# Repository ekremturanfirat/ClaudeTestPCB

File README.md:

# PCBDesignWClaude — 3-Phase BLDC ESC (ESP32-WROOM-32E)

KiCad project for a 3-phase brushless motor ESC.

- **MCU:** ESP32-WROOM-32E, soldered SMD directly onto the PCB (no plug-in module)
- **Input:** 12–36V DC
- **Target continuous phase current:** ~5–10A
- **Control/telemetry:** UART + CAN bus
- Design follows [METU PowerLab PCB design rules](https://github.com/odtu/Powerlab/blob/master/KiCAD/PCB_DESIGN_RULES.md)
  and uses parts exclusively from [PowerLabKiCadLibraries](https://github.com/odtu/PowerLabKiCadLibraries).

## Status
- [x] GitHub repo created
- [x] ESP32-WROOM-32E added to PowerLabKiCadLibraries (odtu/PowerLabKiCadLibraries#2, merged)
- [x] Library additions + fixes (power symbols, mounting holes, fiducials, test pads, net ties, ESP32 footprint fix): odtu/PowerLabKiCadLibraries#3 (merged)
- [x] Schematic Rev B: full rebuild per the PowerLab rules; kicad-cli ERC 0 errors, netlist verified (see [hardware/ARCHITECTURE.md](hardware/ARCHITECTURE.md))
- [x] Library fixes found during layout (exposed pads, mask margins, logo/QR graphics, ESP32 3D model): odtu/PowerLabKiCadLibraries#5 (merged)
- [x] PCB Rev B: 4 layers, 100 × 90 mm; kicad-cli DRC 0 errors / 0 unconnected / 0 parity (see [hardware/ARCHITECTURE.md](hardware/ARCHITECTURE.md#pcb-rev-b))
- [x] Fab outputs: Gerber + drill zip, BOM, position file, assembly drawings in [hardware/fab](hardware/fab/README.md)

## Layout
- `hardware/` — KiCad project

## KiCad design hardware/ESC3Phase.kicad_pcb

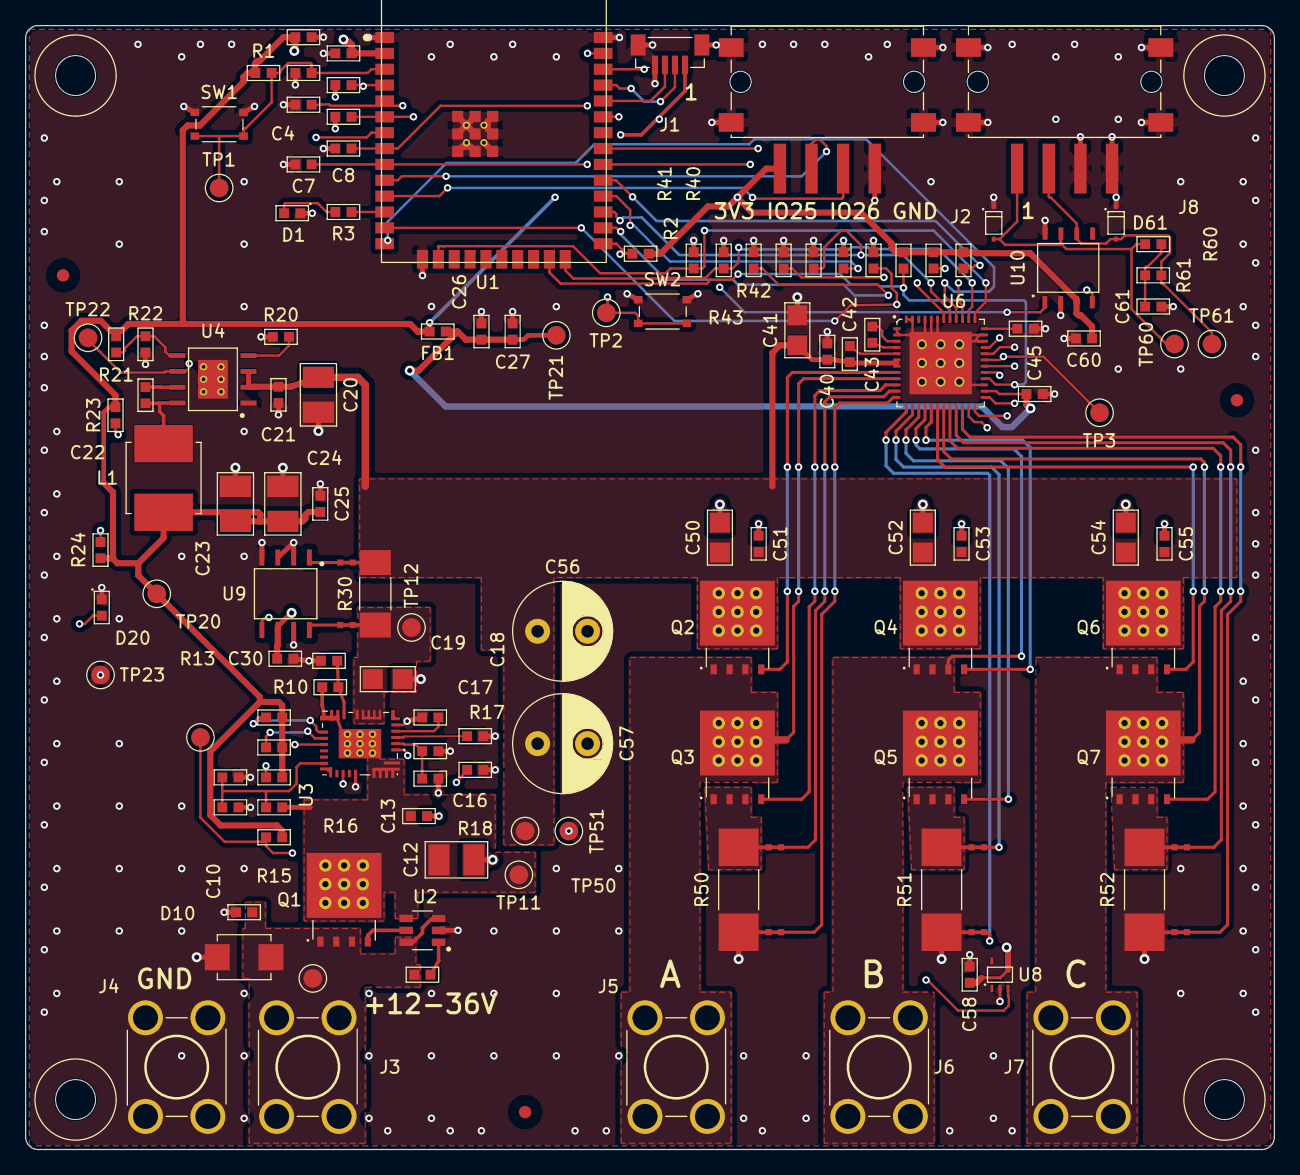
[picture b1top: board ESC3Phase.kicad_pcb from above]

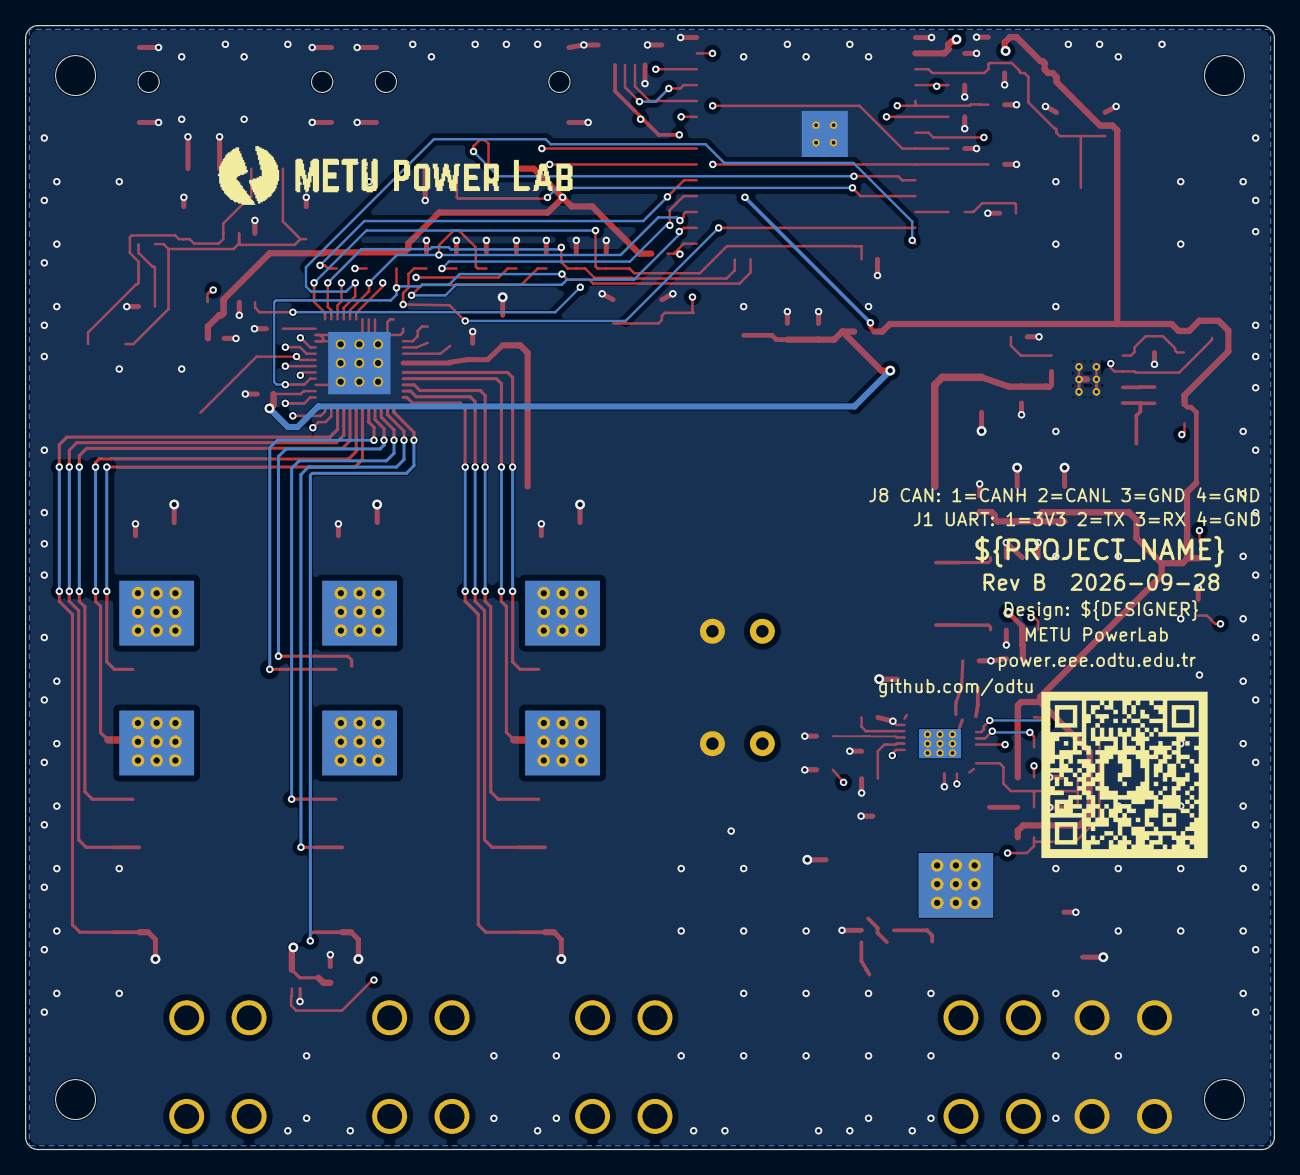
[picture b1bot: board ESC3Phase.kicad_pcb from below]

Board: 4 copper layers, 100.0 x 90.0 mm, 141 parts (2 on the bottom side), 79 nets.

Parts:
C1: 22 µF; 0603_Medium
C2, C14, C18, C22, C25, C27, C30, C45, C58, C60: 100 nF; 0603_Medium
C3, C44: 1 µF; 0603_Medium
C4, C5, C6, C7, C8, C15: 220 pF; 0603_Medium
C10, C13, C21, C40, C51, C53, C55: 100 nF 100V; 0603_Medium
C11: 100 nF 16V; 0603_Medium
C12, C20: 4.7 µF 100V; 1210_Medium
C16: 22 pF; 0603_Medium
C17: 1 nF; 0603_Medium
C19, C41, C50, C52, C54: 10 µF 100V; 1206_Medium
C23, C24: 47 µF; 1210_Medium
C26: 10 µF; 0603_Medium
C42: 1 µF 100V; 0603_Medium
C43: 47 nF 100V; 0603_Medium
C56, C57: 100 µF 63V; 8.00x13.50mm
C61: 4.7 nF; 0603_Medium
D1, D20: Green; 0603_Medium
D10: SMBJ36CA-13-F; DO-214AA
D60, D61: CDSOD323-T24SC; SOD-323
FB1: BLM18EG221SN1D; 0603_Medium
FID1, FID2, FID3: Fiducial_1mm_Mask2mm
H1, H2, H3, H4: M3_NPTH
J1: UART; 2147210040
J2: EXPANSION; 384471-E
J3: VIN+; 7770
J4: GND; 7770
J5, J6, J7: PHASE; 7770
J8: CAN; 384471-E
L1: 4.7µH; 6x5_7mm
LOGO1: METUPowerLab_Logo_30mm
NT1, NT2, NT3, NT4, NT5, NT6, NT7, NT8: NetTie_2_0.5mm
Q1, Q2, Q3, Q4, Q5, Q6, Q7: NTMFS006N08MC; 8-PowerTDFN(5x6mm)
QR1: METUPowerLab_QRCode_13.3mm
R1, R2, R13, R14, R15, R16, R40, R41, R42, R43, R44, R45, R46, R47, R48, R49: 10 kOhm; 0603_Medium
R3, R24: 1 kOhm; 0603_Medium
R10: 120 Ohm; 0603_Medium
R11: 866 kOhm; 0603_Medium
R12: 118 kOhm; 0603_Medium
R17: 3.65 kOhm; 0603_Medium
R18: 1.33 kOhm; 0603_Medium
R20: 54.9 kOhm; 0603_Medium
R21: 110 kOhm; 0603_Medium
R22: 47 kOhm; 0603_Medium
R23: 100 kOhm; 0603_Medium
R30: 5 mOhm; 2010
R50, R51, R52: 2 mOhm; 2512
R60, R61: 56 Ohm; 0603_Medium
SW1: RESET; TL6330AF200Q
SW2: BOOT; TL6330AF200Q
TP1: EN; Pad_D1.5mm
TP2: BOOT; Pad_D1.5mm
TP3: SPI_SCLK; Pad_D1.5mm
TP10: VIN_RAW; Pad_D1.5mm
TP11: +VBUS; Pad_D1.5mm
TP12: +VBUS_EFUSE; Pad_D1.5mm
TP13: EFUSE_PGOOD; Pad_D1.5mm
TP20: +3V3_MCU; Pad_D1.5mm
TP21: +3V3_A; Pad_D1.5mm
TP22: BUCK_PG; Pad_D1.5mm
TP23, TP51: GND; Pad_D1.5mm
TP50: +VBUS_PROT; Pad_D1.5mm
TP60: CANH; Pad_D1.5mm
TP61: CANL; Pad_D1.5mm
U1: ESP32-WROOM-32E
U2: LM74700QDBVRQ1; SOT-23-6_DBV
U3: PTPS16890VMAR; 23-LQFN-CLIP_(VMA)
U4: LMR38020FSDDAR; 8-SOICPower
U6: DRV8323RSRGZT; 48-VQFN
U8: TMP235A4DCKR; SC-70-5
U9: INA240A1DR; 8-SOIC
U10: SN65HVD230DR; 8-SOIC

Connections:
+3V3_A: C26.1, C27.1, C30.1, C45.1, C58.1, FB1.2, TP21.1, U6.26, U8.4, U9.6
+3V3_MCU: C1.1, C2.1, C23.1, C24.1, C25.1, C60.1, FB1.1, J1.1, J2.1, L1.2, R1.1, R2.1, R13.2, R14.2, R15.2, R16.2, R21.1, R23.2, R24.1, R47.2, R48.2, R49.2, TP20.1, U1.2, U10.3
+VBUS: C12.1, C13.1, Q1.3, R10.1, R11.1, TP11.1, U2.4, U3.10, U3.22, U3.23, U3.24
+VBUS_EFUSE: C19.1, NT1.1, R30.1, TP12.1, U3.7, U3.8
+VBUS_PROT: C20.1, C21.1, C40.1, C41.1, C42.1, C50.1, C51.1, C52.1, C53.1, C54.1, C55.1, C56.1, C57.1, NT2.1, Q2.3, Q4.3, Q6.3, R30.2, TP50.1, U4.2, U4.3, U6.6, U6.7
/Communication/CANH: D60.1, J8.1, R60.1, TP60.1, U10.7
/Communication/CANL: D61.1, J8.2, R61.2, TP61.1, U10.6
/Communication/CAN_SPLIT: C61.1, R60.2, R61.1
/DC-Bus Current Sensing/IBUS_SNS_N: NT2.2, U9.1
/DC-Bus Current Sensing/IBUS_SNS_P: NT1.2, U9.8
/Gate Drive/CPH: C43.1, U6.4
/Gate Drive/CPL: C43.2, U6.3
/Gate Drive/DVDD: C44.1, U6.36
/Gate Drive/VCP: C42.2, U6.5
/MCU Core/BOOT: R2.2, SW2.1, TP2.1, U1.25
/MCU Core/EN: C3.1, R1.2, SW1.1, TP1.1, U1.3
/MCU Core/EXP1: J2.2, U1.10
/MCU Core/EXP2: J2.3, U1.11
/MCU Core/LED_STATUS: R3.1, U1.12
/MCU Core/UART_RXD: J1.3, U1.34
/MCU Core/UART_TXD: J1.2, U1.35
/Power Input & Protection/EFUSE_DVDT: C18.1, U3.4
/Power Input & Protection/EFUSE_EN: C15.1, R11.2, R12.1, U3.16
/Power Input & Protection/EFUSE_ILIM: R18.1, U3.1
/Power Input & Protection/EFUSE_IMON: C16.1, R17.1, U3.2
/Power Input & Protection/EFUSE_IREF: C17.1, U3.3
/Power Input & Protection/EFUSE_PGOOD: R15.1, TP13.1, U3.19
/Power Input & Protection/EFUSE_SCL: R14.1, U3.12
/Power Input & Protection/EFUSE_SDA: R13.1, U3.11
/Power Input & Protection/EFUSE_VDD: C14.1, R10.2, U3.9
/Power Input & Protection/LM_VCAP: C11.2, U2.1
/Power Input & Protection/REVPOL_GATE: Q1.2, U2.5
/Power Stage/Half Bridge A/LS_SRC: NT3.2, Q3.1, R50.1
/Power Stage/Half Bridge B/LS_SRC: NT5.2, Q5.1, R51.1
/Power Stage/Half Bridge C/LS_SRC: NT7.2, Q7.1, R52.1
/Power Supply 3.3 V/BUCK_BOOT: C22.1, U4.7
/Power Supply 3.3 V/BUCK_FB: R21.2, R22.1, U4.5
/Power Supply 3.3 V/BUCK_PG: R23.1, TP22.1, U4.6
/Power Supply 3.3 V/BUCK_RT: R20.1, U4.4
/Power Supply 3.3 V/BUCK_SW: C22.2, L1.1, U4.8
CAN_RX: U1.36, U10.4
CAN_TX: U1.33, U10.1
DRV_ENABLE: R46.1, U1.13, U6.33
EFUSE_NFLT: R16.1, U1.7, U3.13
GHA: Q2.2, U6.8
GHB: Q4.2, U6.17
GHC: Q6.2, U6.18
GLA: Q3.2, U6.10
GLB: Q5.2, U6.15
GLC: Q7.2, U6.20
GND: C1.2, C2.2, C3.2, C4.2, C5.2, C6.2, C7.2, C8.2, C10.2, C12.2, C13.2, C14.2, C15.2, C16.2, C17.2, C18.2, C19.2, C20.2, C21.2, C23.2, C24.2, C25.2, C26.2, C27.2, C30.2, C40.2, C41.2, C44.2, C45.2, C50.2, C51.2, C52.2, C53.2, C54.2, C55.2, C56.2, C57.2, C58.2, C60.2, C61.2, D1.2, D10.2, D20.2, D60.2, D61.2, J1.4, J1.Shield, J2.4, J2.Shield, J4.1, J8.3, J8.4, J8.Shield, NT4.2, NT6.2, NT8.2, R12.2, R17.2, R18.2, R20.2, R22.2, R40.2, R41.2, R42.2, R43.2, R44.2, R45.2, R46.2, R50.2, R51.2, R52.2, SW1.2, SW2.2, TP23.1, TP51.1, U1.1, U1.15, U1.38, U1.39, U2.2, U3.5, U3.21, U4.1, U4.Shield, U6.1, U6.2, U6.27, U6.34, U6.35, U6.43, U6.44, U6.45, U6.47, U6.48, U6.Shield, U8.2, U9.2, U9.3, U9.4, U9.7, U10.2, U10.8
IBUS_SENSE: C4.1, U1.4, U9.5
ISENSE_A: C6.1, U1.8, U6.25
ISENSE_A_N: NT4.1, U6.12
ISENSE_A_P: NT3.1, U6.11
ISENSE_B: C7.1, U1.9, U6.24
ISENSE_B_N: NT6.1, U6.13
ISENSE_B_P: NT5.1, U6.14
ISENSE_C: C8.1, U1.6, U6.23
ISENSE_C_N: NT8.1, U6.22
ISENSE_C_P: NT7.1, U6.21
NFAULT: R47.1, U1.23, U6.28
unnamed: D1.1, R3.2
unnamed: D20.1, R24.2
PHASE_A: J5.1, Q2.1, Q3.3, U6.9
PHASE_B: J6.1, Q4.1, Q5.3, U6.16
PHASE_C: J7.1, Q6.1, Q7.3, U6.19
PWM_AH: R40.1, U1.16, U6.37
PWM_AL: R41.1, U1.24, U6.38
PWM_BH: R42.1, U1.26, U6.39
PWM_BL: R43.1, U1.14, U6.40
PWM_CH: R44.1, U1.27, U6.41
PWM_CL: R45.1, U1.28, U6.42
SPI_NSCS: R49.1, U1.29, U6.32
SPI_SCLK: TP3.1, U1.30, U6.31
SPI_SDI: U1.37, U6.30
SPI_SDO: R48.1, U1.31, U6.29
TEMP_SENSE: C5.1, U1.5, U8.3
VIN_RAW: C10.1, C11.1, D10.1, J3.1, Q1.1, TP10.1, U2.3, U2.6

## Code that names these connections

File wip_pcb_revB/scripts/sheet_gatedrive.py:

"""Gate Drive sheet: DRV8323RS per TI SLVSDJ3D (datasheet-verified connections)."""
import schgen
from parts import vcap, vres, pin_net, pull, G

DRV = 'METUPowerLab_MotorDrivers_BLDC:DRV8323RSRGZT'


def build(sh):
    u = sh.add('U6', DRV, (129.54, 132.08))

    # ---- left side ----
    pin_net(sh, u, 'VM', '+VBUS_PROT')
    pin_net(sh, u, 'VCP', 'VCP')
    pin_net(sh, u, 'nFAULT', 'NFAULT', kind='global', shape='output')
    pin_net(sh, u, 'ENABLE', 'DRV_ENABLE', kind='global', shape='input')
    pin_net(sh, u, 'CPH', 'CPH')
    pin_net(sh, u, 'CPL', 'CPL')
    pin_net(sh, u, 'DVDD', 'DVDD')
    for pin, net in [('INHA', 'PWM_AH'), ('INLA', 'PWM_AL'), ('INHB', 'PWM_BH'), ('INLB', 'PWM_BL'),
                     ('INHC', 'PWM_CH'), ('INLC', 'PWM_CL')]:
        pin_net(sh, u, pin, net, kind='global', shape='input')
    for pin, net, shp in [('SDI', 'SPI_SDI', 'input'), ('SDO', 'SPI_SDO', 'output'), ('SCLK', 'SPI_SCLK', 'input'),
                          ('nSCS', 'SPI_NSCS', 'input')]:
        pin_net(sh, u, pin, net, kind='global', shape=shp)
    (tip, _, _), = [(e[0], 0, 0) for e in sh.stub(u, 'CAL', 1)]
    u.pin_net.setdefault('34', set()).add('GND')
    sh.path([tip, (tip[0], 104.14), (104.14, 104.14)])
    sh.power_symbol('GND', (104.14, 104.14))
    for pin, net in [('SOC', 'ISENSE_C'), ('SOB', 'ISENSE_B'), ('SOA', 'ISENSE_A')]:
        pin_net(sh, u, pin, net, kind='global', shape='output')
    sh.group(u, ['PGND', 'DGND', 'AGND', 'BGND', 'Shield'], 'GND', length=2)

    # ---- right side ----
    pin_net(sh, u, 'VDRAIN', '+VBUS_PROT')
    for ph in 'ABC':
        pin_net(sh, u, f'GH{ph}', f'GH{ph}', kind='global', shape='output')
        pin_net(sh, u, f'SH{ph}', f'PHASE_{ph}', kind='global', shape='bidirectional')
        pin_net(sh, u, f'GL{ph}', f'GL{ph}', kind='global', shape='output')
        pin_net(sh, u, f'SP{ph}', f'ISENSE_{ph}_P', kind='global', shape='input')
        pin_net(sh, u, f'SN{ph}', f'ISENSE_{ph}_N', kind='global', shape='input')
    pin_net(sh, u, 'VREF', '+3V3_A')
    # integrated buck unused -> SLVSDJ3D Table 9-3: "All Pins: Tie to GND"
    sh.group(u, ['VIN', 'nSHD', 'CB', 'SW', 'FB'], 'GND', length=2)
    sh.nc(u, 'NC')   # pin 46: "float or GND"

    # ---- support parts (left column) ----
    x1, x2, x3 = 25.4, 50.8, 76.2
    vcap(sh, 'C40', '100 nF 100V', (x1, 38.1), '+VBUS_PROT')          # VM HF decoupling
    vcap(sh, 'C41', '10 µF 100V 1206', (x2, 38.1), '+VBUS_PROT')      # VM bulk
    vcap(sh, 'C42', '1 µF 0603', (x3, 38.1), '+VBUS_PROT', 'VCP')     # VCP -> VM, 1 uF
    vcap(sh, 'C43', '47 nF 100V', (x1, 66.04), 'CPH', 'CPL')         # charge-pump flying cap
    vcap(sh, 'C44', '1 µF 0603', (x2, 66.04), 'DVDD')                 # DVDD 1 uF to AGND
    vcap(sh, 'C45', '100 nF', (x3, 66.04), '+3V3_A')                   # VREF decoupling
    # pull-downs: PWM inputs + ENABLE default off (plus IO2/IO12 strap levels on the ESP32)
    for i, net in enumerate(['PWM_AH', 'PWM_AL', 'PWM_BH', 'PWM_BL', 'PWM_CH', 'PWM_CL', 'DRV_ENABLE']):
        pull(sh, f'R{40 + i}', '10 kOhm', (38.1, 93.98 + i * 10.16), net, 'GND')
    # pull-ups: open-drain nFAULT/SDO, nSCS idle-high (also ESP32 IO5 strap)
    for i, net in enumerate(['NFAULT', 'SPI_SDO', 'SPI_NSCS']):
        pull(sh, f'R{47 + i}', '10 kOhm', (83.82, 93.98 + i * 10.16), net, '+3V3_MCU')

    sh.text('LAYOUT: C40/C41 right at U6 VM pin, short wide path to PGND.\n'
            'LAYOUT: C42 (VCP-VM) and C43 (CPH-CPL) as close as possible to U6.\n'
            'LAYOUT: C44 at DVDD, C45 at VREF, both with short return to AGND.\n'
            'LAYOUT: Route GHx/SHx and GLx/PGND as tight pairs; minimize gate loops.\n'
            'LAYOUT: ISENSE_x_P/N as Kelvin pairs from the shunt net ties.\n'
            'LAYOUT: Thermal pad: via array to GND plane.',
            (12.7, 170.18), size=1.27)
    return u

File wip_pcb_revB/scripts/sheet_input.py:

"""Power Input: connectors, TVS, reverse-polarity ideal diode (LM74700-Q1), eFuse (TPS16890).

LM74700-Q1 per TI SNOSD17G: ANODE/EN on the input, MOSFET source to input, drain to output,
CVCAP >= 0.1 uF between VCAP and ANODE.
TPS16890 per TI SLVSHO1A (standalone): VDD 150 Ohm/0.22 uF recommended (120 Ohm/100 nF used, nearest
library values), EN/UVLO 866k/118k -> 10.1 V rising (internal VIN_UV_FLT default 10.66 V dominates),
IMON 3.65k -> IOCP = 1 V / (18.18 uA/A x 3.65k) = 15.1 A, ILIM 1.33k (Eq. 25), IREF 1 nF, IMON 22 pF,
dVdT 100 nF -> 0.5 V/ms (inrush << 0.5 A startup limit), WP# to GND, ADDR0/1 open (addr 0x40).
"""
from parts import vcap, vres, pin_net, pull, G, R, FP_R0603
from sheet_mcu import testpoint

TERM = 'METUPowerLab_Connectors_ScrewTerminals:7770'
TVS = 'METUPowerLab_Diodes_TVSDiodes:SMBJ36CA-13-F'
LM = 'METUPowerLab_CircuitProtections_IdealDiodes:LM74700QDBVRQ1'
FET = 'METUPowerLab_Transistors_MOSFETs:NTMFS006N08MC'
EFUSE = 'METUPowerLab_CircuitProtections_eFuses:PTPS16890VMAR'


def build(sh):
    # ---- input connectors ----
    j3 = sh.add('J3', TERM, (17.78, 50.8), value='VIN+')
    sh.power_turn(j3, '1', 'VIN_RAW', out=2, turn=2)
    j4 = sh.add('J4', TERM, (17.78, 71.12), value='GND')
    sh.conn(j4, '1', 'GND', style='power', length=2)
    sh.flag_net('VIN_RAW', (254.0, 124.46))
    sh.flag_label('EFUSE_VDD', (254.0, 144.78))
    # ---- surge TVS + input cap ----
    d = sh.add('D10', TVS, (50.8, 60.96), rot=270)
    sh.conn(d, '1', 'VIN_RAW', style='power', length=1)
    sh.conn(d, '2', 'GND', style='power', length=1)
    vcap(sh, 'C10', '100 nF 100V', (78.74, 60.96), 'VIN_RAW')
    # ---- reverse polarity: Q1 source = input side ----
    q1 = sh.add('Q1', FET, (111.76, 50.8), rot=270, mirror='x')      # S left (input), D right, G down
    sh.power_turn(q1, 'S', 'VIN_RAW', out=2, turn=2)
    sh.power_turn(q1, 'D', '+VBUS', out=2, turn=2)
    pin_net(sh, q1, 'G', 'REVPOL_GATE', length=1)
    u2 = sh.add('U2', LM, (111.76, 88.9))
    sh.group(u2, ['ANODE', 'EN'], 'VIN_RAW', length=2)
    pin_net(sh, u2, 'GND', 'GND', length=1)
    pin_net(sh, u2, 'GATE', 'REVPOL_GATE')
    pin_net(sh, u2, 'CATHODE', '+VBUS')
    pin_net(sh, u2, 'VCAP', 'LM_VCAP')
    vcap(sh, 'C11', '100 nF', (86.36, 111.76), 'VIN_RAW', 'LM_VCAP')     # CVCAP between VCAP and ANODE
    sh.text('C11: VCAP-ANODE, <= 15 V (SNOSD17G)', (104.14, 114.3), size=1.0)
    vcap(sh, 'C12', '4.7 µF', (144.78, 60.96), '+VBUS')
    vcap(sh, 'C13', '100 nF 100V', (165.1, 60.96), '+VBUS')
    sh.flag_net('+VBUS', (254.0, 134.62))

    # ---- eFuse ----
    u3 = sh.add('U3', EFUSE, (210.82, 132.08))
    sh.group(u3, ['10', '22', '23', '24'], '+VBUS', length=2)
    pin_net(sh, u3, 'VDD', 'EFUSE_VDD')
    pin_net(sh, u3, 'EN/UVLO', 'EFUSE_EN')
    sh.nc(u3, 'SWEN')
    pin_net(sh, u3, 'SDA', 'EFUSE_SDA')
    pin_net(sh, u3, 'SCL', 'EFUSE_SCL')
    pin_net(sh, u3, 'GND', 'GND', length=1)
    sh.group(u3, ['7', '8'], '+VBUS_EFUSE', length=2)
    pin_net(sh, u3, 'PGOOD', 'EFUSE_PGOOD')
    pin_net(sh, u3, 'FLT', 'EFUSE_NFLT', kind='global', shape='output')
    pin_net(sh, u3, 'IMON', 'EFUSE_IMON')
    pin_net(sh, u3, 'ILIM', 'EFUSE_ILIM')
    pin_net(sh, u3, 'IREF', 'EFUSE_IREF')
    pin_net(sh, u3, 'dV/dT', 'EFUSE_DVDT')
    pin_net(sh, u3, 'WP#', 'GND', length=1)
    for n in ('17', 'AUX/EEDATA/_GPIO2', 'TEMP/EECLK/_GPIO1', 'ADDR0', 'ADDR1'):
        sh.nc(u3, n)
    # eFuse support parts (left column)
    vres(sh, 'R10', '120 Ohm', (25.4, 106.68), '+VBUS', 'EFUSE_VDD')
    vcap(sh, 'C14', '100 nF 100V', (25.4, 132.08), 'EFUSE_VDD')
    vres(sh, 'R11', '866 kOhm', (50.8, 106.68), '+VBUS', 'EFUSE_EN')
    vres(sh, 'R12', '118 kOhm', (50.8, 132.08), 'EFUSE_EN')
    vcap(sh, 'C15', '220 pF', (68.58, 132.08), 'EFUSE_EN')
    pull(sh, 'R13', '10 kOhm', (134.62, 127.0), 'EFUSE_SDA', '+3V3_MCU')
    pull(sh, 'R14', '10 kOhm', (134.62, 137.16), 'EFUSE_SCL', '+3V3_MCU')
    pull(sh, 'R15', '10 kOhm', (134.62, 147.32), 'EFUSE_PGOOD', '+3V3_MCU')
    pull(sh, 'R16', '10 kOhm', (134.62, 157.48), 'EFUSE_NFLT', '+3V3_MCU')
    # eFuse support parts (right column)
    vres(sh, 'R17', '3.65 kOhm', (261.62, 50.8), 'EFUSE_IMON')
    vcap(sh, 'C16', '22 pF', (279.4, 50.8), 'EFUSE_IMON')
    vres(sh, 'R18', '1.33 kOhm', (261.62, 76.2), 'EFUSE_ILIM')
    vcap(sh, 'C17', '1 nF ', (279.4, 76.2), 'EFUSE_IREF')
    vcap(sh, 'C18', '100 nF', (243.84, 50.8), 'EFUSE_DVDT')
    vcap(sh, 'C19', '10 µF 100V 1206', (193.04, 38.1), '+VBUS_EFUSE')
    for i, (net, x) in enumerate((('VIN_RAW', 33.02), ('+VBUS', 63.5), ('+VBUS_EFUSE', 93.98))):
        testpoint(sh, f'TP{10 + i}', net, (x, 157.48))
    testpoint(sh, 'TP13', 'EFUSE_PGOOD', (185.42, 157.48))
    sh.text('LAYOUT: D10 and C10 directly at J3/J4. Wide pours for VIN_RAW, +VBUS, +VBUS_EFUSE (up to 15 A).\n'
            'LAYOUT: C11 at U2 VCAP/ANODE. U2 close to Q1 gate/source.\n'
            'LAYOUT: C14 at U3 VDD, C16/C17/C18/R17/R18 at their U3 pins, returns to U3 GND.\n'
            'LAYOUT: U3 exposed pad is IN (not GND): via array into the +VBUS pour.',
            (12.7, 170.18))

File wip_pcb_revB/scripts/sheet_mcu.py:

"""MCU Core: ESP32-WROOM-32E per Espressif datasheet v2.1 / hardware design guidelines."""
from parts import vcap, vres, pin_net, pull, G, R, FP_R0603, cap_fp, C, GLOBAL_NETS
import parts

ESP = 'METUPowerLab_Microcontrollers_ESP32:ESP32-WROOM-32E'
SW = 'METUPowerLab_Switches_TactileSwitches:TL6330AF200Q'
J1x4 = 'METUPowerLab_Connectors_SignalConnectors:2147210040'
JEXP = 'METUPowerLab_Connectors_SignalConnectors:384471-E'
LED_G = 'METUPowerLab_LEDs_SurfaceMounts:Green '
TP = 'METUPowerLab_TestPoints_SurfaceMounts:TestPoint_Pad'
FP_LED = 'METUPowerLab_LEDs_SurfaceMounts:0603_Medium'
FP_TP = 'METUPowerLab_TestPoints_SurfaceMounts:Pad_D1.5mm'


def testpoint(sh, ref, net, at):
    tp = sh.add(ref, TP, at, footprint=FP_TP, value=net)
    kind = 'global' if net in GLOBAL_NETS else 'label'
    if net == 'GND':
        sh.conn(tp, '1', net, style='power', length=1)
    elif net in parts.POWER_NETS:            # rail: go down, then sideways, arrow clear of the TP circle
        (end, _, pin), = sh.stub(tp, '1', 1)
        tp.pin_net.setdefault('1', set()).add(net)
        side = (round(end[0] - G * 3, 4), end[1])
        sh.wire(end, side)
        sh.power_symbol(net, side)
    else:
        sh.conn(tp, '1', net, style='label', kind=kind, shape='passive' if kind == 'global' else 'bidirectional',
                length=1, jog=-1)
    return tp


def build(sh):
    u = sh.add('U1', ESP, (139.7, 101.6))
    # ---- left side ----
    pin_net(sh, u, '2', '+3V3_MCU')
    pin_net(sh, u, 'EN', 'EN')
    pin_net(sh, u, '1', 'GND', length=1)
    for pin, net, shp in [('SENSOR_VP', 'IBUS_SENSE', 'input'), ('SENSOR_VN', 'TEMP_SENSE', 'input'),
                          ('IO34', 'ISENSE_C', 'input'), ('IO35', 'EFUSE_NFLT', 'input'),
                          ('IO32', 'ISENSE_A', 'input'), ('IO33', 'ISENSE_B', 'input'),
                          ('IO14', 'DRV_ENABLE', 'output'), ('IO12', 'PWM_BL', 'output'),
                          ('IO13', 'PWM_AH', 'output')]:
        pin_net(sh, u, pin, net, kind='global', shape=shp)
    pin_net(sh, u, 'IO25', 'EXP1')
    pin_net(sh, u, 'IO26', 'EXP2')
    pin_net(sh, u, 'IO27', 'LED_STATUS')
    sh.group(u, ['15', '39'], 'GND', length=2)
    # ---- right side ----
    for pin, net, shp in [('IO15', 'NFAULT', 'input'), ('IO2', 'PWM_AL', 'output'), ('IO4', 'PWM_BH', 'output'),
                          ('IO16', 'PWM_CH', 'output'), ('IO17', 'PWM_CL', 'output'), ('IO5', 'SPI_NSCS', 'output'),
                          ('IO18', 'SPI_SCLK', 'output'), ('IO19', 'SPI_SDO', 'input'), ('IO21', 'CAN_TX', 'output'),
                          ('IO22', 'CAN_RX', 'input'), ('IO23', 'SPI_SDI', 'output')]:
        pin_net(sh, u, pin, net, kind='global', shape=shp)
    pin_net(sh, u, 'IO0', 'BOOT')
    pin_net(sh, u, 'RXD0', 'UART_RXD')
    pin_net(sh, u, 'TXD0', 'UART_TXD')
    pin_net(sh, u, '38', 'GND', length=1)
    for n in ('17', '18', '19', '20', '21', '22', '32'):
        sh.nc(u, n)

    # ---- supply decoupling (DS fig. 9: 22 uF + 0.1 uF at 3V3) ----
    vcap(sh, 'C1', '22 µF', (25.4, 30.48), '+3V3_MCU')
    vcap(sh, 'C2', '100 nF', (45.72, 30.48), '+3V3_MCU')
    # ---- EN reset: 10k pull-up + 1 uF (DS sec. 9), RESET button ----
    vres(sh, 'R1', '10 kOhm', (25.4, 60.96), '+3V3_MCU', 'EN')
    vcap(sh, 'C3', '1 µF 0603', (45.72, 60.96), 'EN')
    s1 = sh.add('SW1', SW, (68.58, 58.42), value='RESET')
    sh.conn(s1, '1', 'EN', style='label', length=1)
    sh.conn(s1, '2', 'GND', style='power', length=1)
    # ---- IO0 boot strap: 10k pull-up, BOOT button to GND ----
    vres(sh, 'R2', '10 kOhm', (25.4, 83.82), '+3V3_MCU', 'BOOT')
    s2 = sh.add('SW2', SW, (68.58, 81.28), value='BOOT')
    sh.conn(s2, '1', 'BOOT', style='label', length=1)
    sh.conn(s2, '2', 'GND', style='power', length=1)
    # ---- ADC input filter caps (<=1 nF: INA240 / TMP235 max capacitive load) ----
    for i, net in enumerate(['IBUS_SENSE', 'TEMP_SENSE', 'ISENSE_A', 'ISENSE_B', 'ISENSE_C']):
        vcap(sh, f'C{4 + i}', '220 pF', (25.4 + i * 17.78, 121.92), net)

    # ---- UART / programming header J1: 1 +3V3, 2 TXD (ESP out), 3 RXD (ESP in), 4 GND ----
    j1 = sh.add('J1', J1x4, (210.82, 45.72), value='UART')
    sh.power_turn(j1, '1', '+3V3_MCU', out=2, turn=2)
    sh.conn(j1, '2', 'UART_TXD', style='label', length=2)
    sh.conn(j1, '3', 'UART_RXD', style='label', length=2)
    sh.group(j1, ['4', 'Shield'], 'GND', length=2)
    # ---- expansion header J2 (hall / encoder): 1 +3V3, 2 EXP1, 3 EXP2, 4 GND ----
    j2 = sh.add('J2', JEXP, (210.82, 83.82), value='EXPANSION')
    sh.power_turn(j2, '1', '+3V3_MCU', out=2, turn=2)
    sh.conn(j2, '2', 'EXP1', style='label', length=2)
    sh.conn(j2, '3', 'EXP2', style='label', length=2)
    sh.group(j2, ['4', 'Shield'], 'GND', length=2)
    # ---- status LED ----
    r = sh.add('R3', R + '1 kOhm', (205.74, 119.38), footprint=FP_R0603)
    sh.conn(r, '1', 'LED_STATUS', style='label', length=1)
    d = sh.add('D1', LED_G, (228.6, 119.38), footprint=FP_LED)
    sh.wire(r.pin_pos(r.pins('2')[0]), d.pin_pos(d.pins('1')[0]))
    r.pin_net['2'] = {'LED_A'}; d.pin_net['1'] = {'LED_A'}
    sh.conn(d, '2', 'GND', style='power', length=1)
    # ---- test points ----
    testpoint(sh, 'TP1', 'EN', (213.36, 149.86))
    testpoint(sh, 'TP2', 'BOOT', (238.76, 149.86))
    testpoint(sh, 'TP3', 'SPI_SCLK', (264.16, 149.86))

    sh.text('LAYOUT: Module antenna at the board edge, antenna outside the board or a cut-out\n'
            '        on both sides (Espressif HDG sec. 1.4.8). Keep copper, parts and traces out of the keepout.\n'
            'LAYOUT: C1/C2 right at U1 pin 2 (3V3), via to GND at the cap pad.\n'
            'LAYOUT: C3/R1 close to U1 pin 3 (EN). C4-C8 close to the ESP32 ADC pins.\n'
            'LAYOUT: Thermal pad (pin 39): via array to the GND plane.',
            (12.7, 142.24))

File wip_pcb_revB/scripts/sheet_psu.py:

"""Power Supply: LMR38020 buck to 3.3 V (TI SNVSC40E), ferrite-filtered +3V3_A rail."""
from parts import vcap, vres, pin_net, pull, G, R, FP_R0603
from sheet_mcu import testpoint, LED_G, FP_LED

BUCK = 'METUPowerLab_Regulators_BuckConverters:LMR38020FSDDAR'
IND = 'METUPowerLab_Inductors_SurfaceMounts:4.7µH'
FB = 'METUPowerLab_CircuitProtections_FerriteBeads:BLM18EG221SN1D'
FP_FB = 'METUPowerLab_CircuitProtections_FerriteBeads:0603_Medium'


def build(sh):
    u = sh.add('U4', BUCK, (101.6, 88.9))
    sh.group(u, ['VIN', 'EN'], '+VBUS_PROT', length=2)  # SNVSC40E: EN may tie directly to VIN
    pin_net(sh, u, 'RT/SYNC', 'BUCK_RT')
    sh.group(u, ['GND', 'Shield'], 'GND', length=2)
    pin_net(sh, u, 'BOOT', 'BUCK_BOOT')
    pin_net(sh, u, 'SW', 'BUCK_SW')
    pin_net(sh, u, 'FB', 'BUCK_FB')
    pin_net(sh, u, 'PG', 'BUCK_PG')
    # input caps (>= 4.7 uF effective, rated 2x VIN) + 100 nF at the pins
    vcap(sh, 'C20', '4.7 µF', (25.4, 45.72), '+VBUS_PROT')
    vcap(sh, 'C21', '100 nF 100V', (50.8, 45.72), '+VBUS_PROT')
    vres(sh, 'R20', '54.9 kOhm', (50.8, 106.68), 'BUCK_RT')          # ~480 kHz (SNVSC40E Eq. 2)
    vcap(sh, 'C22', '100 nF', (160.02, 50.8), 'BUCK_BOOT', 'BUCK_SW')  # CBOOT 0.1 uF, >= 16 V
    l1 = sh.add('L1', IND, (175.26, 76.2))
    sh.conn(l1, '1', 'BUCK_SW', style='label', length=1, jog=-1)
    sh.power_turn(l1, '2', '+3V3_MCU', out=2, turn=2)
    # output caps + feedback divider: Vout = 1.0 V x (1 + 110k / 47k) = 3.34 V
    vcap(sh, 'C23', '47 µF', (200.66, 88.9), '+3V3_MCU')
    vcap(sh, 'C24', '47 µF', (220.98, 88.9), '+3V3_MCU')
    vcap(sh, 'C25', '100 nF', (241.3, 88.9), '+3V3_MCU')
    vres(sh, 'R21', '110 kOhm', (175.26, 109.22), '+3V3_MCU', 'BUCK_FB')
    vres(sh, 'R22', '47 kOhm', (175.26, 134.62), 'BUCK_FB')
    pull(sh, 'R23', '100 kOhm', (200.66, 124.46), 'BUCK_PG', '+3V3_MCU')
    # +3V3_A: ferrite-filtered analog rail (DRV8323 VREF, INA240, TMP235)
    fb = sh.add('FB1', FB, (38.1, 139.7), footprint=FP_FB)
    sh.power_turn(fb, '1', '+3V3_MCU', out=3, turn=2)
    sh.power_turn(fb, '2', '+3V3_A', out=3, turn=2)
    vcap(sh, 'C26', '10 µF', (63.5, 142.24), '+3V3_A')
    vcap(sh, 'C27', '100 nF', (83.82, 142.24), '+3V3_A')
    # power LED
    r = sh.add('R24', R + '1 kOhm', (116.84, 139.7), footprint=FP_R0603)
    sh.power_turn(r, '1', '+3V3_MCU', out=2, turn=2)
    d = sh.add('D20', LED_G, (137.16, 139.7), footprint=FP_LED)
    sh.wire(r.pin_pos(r.pins('2')[0]), d.pin_pos(d.pins('1')[0]))
    r.pin_net['2'] = {'PWR_LED_A'}
    d.pin_net['1'] = {'PWR_LED_A'}
    sh.conn(d, '2', 'GND', style='power', length=1)
    for i, (net, x) in enumerate((('+3V3_MCU', 213.36), ('+3V3_A', 236.22), ('BUCK_PG', 259.08), ('GND', 279.4))):
        testpoint(sh, f'TP{20 + i}', net, (x, 147.32))
    sh.flag_net('+3V3_MCU', (218.44, 50.8))
    sh.flag_net('+3V3_A', (218.44, 63.5))
    sh.text('LAYOUT: C21 (100 nF) and C20 right at U4 VIN/GND, smallest input loop (SNVSC40E 9.5).\n'
            'LAYOUT: C22 close to BOOT/SW with short wide traces. Keep the SW node (U4 pin 8 - L1) small.\n'
            'LAYOUT: R21/R22 at the FB pin; route the 3V3 sense line away from SW.\n'
            'LAYOUT: Thermal pad: >= 4x3 via array to GND.',
            (12.7, 162.56))

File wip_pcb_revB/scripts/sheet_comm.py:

"""Communication: SN65HVD230 CAN transceiver per TI SLOS346O."""
from parts import vcap, pin_net, G, R, FP_R0603
from sheet_mcu import testpoint

CAN = 'METUPowerLab_Interfaces_CANBusBridges:SN65HVD230DR'
TVS = 'METUPowerLab_Diodes_TVSDiodes:CDSOD323-T24SC'
JCAN = 'METUPowerLab_Connectors_SignalConnectors:384471-E'


def build(sh):
    u = sh.add('U10', CAN, (101.6, 106.68))
    pin_net(sh, u, 'VCC', '+3V3_MCU')
    sh.nc(u, 'VREF')                                   # SLOS346O 10.3.1: may be left floating
    pin_net(sh, u, 'D', 'CAN_TX', kind='global', shape='input')
    pin_net(sh, u, 'R', 'CAN_RX', kind='global', shape='output')
    sh.group(u, ['RS', 'GND'], 'GND', length=2)      # RS strong pull-down = high-speed mode
    pin_net(sh, u, 'CANH', 'CANH', length=4)
    pin_net(sh, u, 'CANL', 'CANL', length=4)
    vcap(sh, 'C60', '100 nF', (50.8, 55.88), '+3V3_MCU')
    # split termination (optional per TI 11.2.1.1): 2 x 56 Ohm + 4.7 nF to GND
    r1 = sh.add('R60', R + '56 Ohm', (160.02, 76.2), rot=270, footprint=FP_R0603)
    r2 = sh.add('R61', R + '56 Ohm', (160.02, 101.6), rot=270, footprint=FP_R0603)
    for p_, top, bot in ((r1, 'CANH', 'CAN_SPLIT'), (r2, 'CAN_SPLIT', 'CANL')):
        sh.conn(p_, '1', top, style='label', length=1)
        sh.conn(p_, '2', bot, style='label', length=1)
    vcap(sh, 'C61', '4.7 nF', (185.42, 88.9), 'CAN_SPLIT')
    # ESD: 24 V bidirectional TVS per line
    for ref, net, x in (('D60', 'CANH', 160.02), ('D61', 'CANL', 190.5)):
        d = sh.add(ref, TVS, (x, 134.62), rot=270)
        sh.conn(d, '1', net, style='label', length=1)
        sh.conn(d, '2', 'GND', style='power', length=1)
    # bus connector J8: 1 CANH, 2 CANL, 3 GND, 4 GND
    j = sh.add('J8', JCAN, (228.6, 99.06), value='CAN')
    sh.conn(j, '1', 'CANH', style='label', length=2)
    sh.conn(j, '2', 'CANL', style='label', length=2)
    sh.group(j, ['3', '4', 'Shield'], 'GND', length=2)
    testpoint(sh, 'TP60', 'CANH', (215.9, 147.32))
    testpoint(sh, 'TP61', 'CANL', (241.3, 147.32))
    sh.text('LAYOUT: C60 right at U10 VCC pin.\n'
            'LAYOUT: CANH/CANL as a tightly coupled pair to J8, same layer, no stubs.\n'
            'LAYOUT: D60/D61 at the connector, short path to GND. R60/R61/C61 near J8.',
            (12.7, 160.02))

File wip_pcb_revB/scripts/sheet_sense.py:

"""Current Sensing: DC-bus shunt + INA240A1 (TI SBOS662C), unidirectional, Kelvin via net ties.

Gain 20 V/V x 5 mOhm = 100 mV/A -> 1.5 V at 15 A (usable <= 3.1 V on a 3.3 V supply).
"""
from parts import vcap, pin_net, G

SHUNT = 'METUPowerLab_Resistors_ShuntResistors:5 mOhm '
NT = 'METUPowerLab_NetTies_SurfaceMounts:NetTie_2_0.5mm'
INA = 'METUPowerLab_Amplifiers_CurrentSenses:INA240A1DR'
FP_SHUNT = 'METUPowerLab_Resistors_ShuntResistors:2010'


def build(sh):
    rs = sh.add('R30', SHUNT, (101.6, 60.96), footprint=FP_SHUNT)
    force1, force2 = [p for p in rs.pins('1') if p['ang'] == 0][0], [p for p in rs.pins('2') if p['ang'] == 180][0]
    sense1, sense2 = [p for p in rs.pins('1') if p['ang'] == 90][0], [p for p in rs.pins('2') if p['ang'] == 90][0]
    sh.power_turn(rs, '1', '+VBUS_EFUSE', out=2, turn=2) if False else None
    # force pins -> power rails (stub out, turn up)
    for pin, net, idx in ((force1, '+VBUS_EFUSE', 0), (force2, '+VBUS_PROT', 1)):
        tip = rs.pin_pos(pin)
        dx, dy = rs.pin_out(pin)
        end = (round(tip[0] + dx * G * 2, 4), tip[1])
        top = (end[0], round(end[1] - G * 2, 4))
        sh.path([tip, end, top])
        sh.power_symbol(net, top)
        rs.pin_net.setdefault(pin['number'], set()).add(net)
    # Kelvin taps -> net ties -> INA240 inputs
    nt_p = sh.add('NT1', NT, (91.44, 78.74), rot=270)
    nt_n = sh.add('NT2', NT, (111.76, 78.74), rot=270)
    for pin, nt, x in ((sense1, nt_p, 91.44), (sense2, nt_n, 111.76)):
        tip = rs.pin_pos(pin)
        ntp1 = nt.pin_pos(nt.pins('1')[0])
        net = '+VBUS_EFUSE' if nt is nt_p else '+VBUS_PROT'
        sh.path([tip, (tip[0], 68.58), (x, 68.58), ntp1])
        sh.power_symbol(net, (x, 68.58))
        nt.pin_net['1'] = {net}
        rs.pin_net.setdefault(pin['number'], set()).add(net)
    sh.conn(nt_p, '2', 'IBUS_SNS_P', style='label', length=1, jog=1)
    sh.conn(nt_n, '2', 'IBUS_SNS_N', style='label', length=1, jog=1)

    u = sh.add('U9', INA, (165.1, 104.14), fields={'_rv': (172.72, 95.25, 172.72, 97.79)})
    pin_net(sh, u, '8', 'IBUS_SNS_P')
    pin_net(sh, u, '1', 'IBUS_SNS_N')
    pin_net(sh, u, '6', '+3V3_A', length=1)
    sh.group(u, ['2', '3', '7'], 'GND', length=1)
    u.pin_net.setdefault('4', set()).add('GND')        # pin 4 (NC) stacked on GND in the library symbol
    pin_net(sh, u, '5', 'IBUS_SENSE', kind='global', shape='output')
    vcap(sh, 'C30', '100 nF', (137.16, 81.28), '+3V3_A')
    sh.flag_net('+VBUS_PROT', (205.74, 60.96))
    sh.text('LAYOUT: R30 in the +VBUS_EFUSE -> +VBUS_PROT pour, full width.\n'
            'LAYOUT: Kelvin: NT1/NT2 at the R30 pads; route IBUS_SNS_P/N as a tight pair to U9.\n'
            'LAYOUT: C30 right at U9 V+ (pin 6).',
            (12.7, 160.02))
